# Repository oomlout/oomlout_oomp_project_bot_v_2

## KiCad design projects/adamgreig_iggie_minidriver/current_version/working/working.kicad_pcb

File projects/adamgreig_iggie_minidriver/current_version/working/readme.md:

# iggie
 
## summary 
* id: adamgreig_iggie_minidriver
* user: adamgreig
* name: iggie
* board: minidriver
* repo: https://github.com/adamgreig/iggie
* src_file_repo_kicad_pcb: minidriver/pcb/minidriver.kicad_pcb
* src_file_repo_kicad_pcb_link: https://github.com/adamgreig/iggie/tree/master/minidriver/pcb/minidriver.kicad_pcb
* src_file_repo_kicad_sch: minidriver/pcb/minidriver.kicad_sch
* src_file_repo_kicad_sch_link: https://github.com/adamgreig/iggie/tree/master/minidriver/pcb/minidriver.kicad_sch

* src_file_repo_sch: load/load.sch
* src_file_repo_sch_link: https://github.com/adamgreig/iggie/tree/master/load/load.sch
* full details link: https://github.com/oomlout/oomlout_oomp_project_bot_v_2/tree/main/projects/adamgreig_iggie_minidriver/current_version/working  

## schematic  
  
[schematic (pdf)](working_schematic.pdf) 

## pcb  

[board (pdf)](working.pdf)  

## bom_schematic
| Ref | Qnty | Value | Cmp name | Footprint | Description | Vendor | DNP | 
| --- | --- | --- | --- | --- | --- | --- | --- | 
| C1 | 1 | 4Âµ7 | C | agg:1206 |  |  |  | 
| C2, C4, C5 | 3 | 100n | C | agg:0402 |  |  |  | 
| C3 | 1 | 10Âµ | C | agg:0603 |  |  |  | 
| D1 | 1 | LED | LED | agg:0603-LED |  |  |  | 
| IC1 | 1 | TSR1-2433 | TSR1 | agg:TSR1 | TSR1 Switch Mode Regulators |  |  | 
| IC2 | 1 | STM32G070KBT6 | STM32G0xxKx | agg:LQFP-32 | STM32G0 32 pin LQFP package |  |  | 
| IC3 | 1 | 74HC4514 | 74HC4514 | agg:SOIC-24-W | 4-to-16 line decoder/demultiplexer with input latches |  |  | 
| J1 | 1 | HV_IN | CONN_01x03 | agg:MOLEX-KK-254P-03 |  |  |  | 
| J2 | 1 | HV_PSU | CONN_01x04 | agg:MOLEX-KK-254P-04 |  |  |  | 
| J3, J6, J7 | 3 | SJ2 | SJ2 | agg:SJ2 |  |  |  | 
| J4 | 1 | ANODES | CONN_01x04 | agg:MOLEX-KK-254P-04 |  |  |  | 
| J5 | 1 | CATHODES | CONN_01x04 | agg:MOLEX-KK-254P-04 |  |  |  | 
| P1 | 1 | SWD | SWD | agg:FTSH-105-01-L-DV-K | Serial Wire Debug Port |  |  | 
| Q1, Q2, Q4, Q6, Q7, Q8, Q10, Q12 | 8 | DMN60H080DS-7 | NFET | agg:SOT-23 | Generic N-channel FET |  |  | 
| Q3, Q5, Q9, Q11 | 4 | PBHV9050T,215 | PNP | agg:SOT-23 | PNP BJT Transistor |  |  | 
| R1, R2 | 2 | 100 | R | agg:0402 |  |  |  | 
| R3, R4, R9, R10 | 4 | 1M | R | agg:1206 |  |  |  | 
| R5, R6, R11, R12 | 4 | 10k | R | agg:1206 |  |  |  | 
| R7, R8, R13, R14 | 4 | 93k1 | R | agg:1206 |  |  |  | 
| R15 | 1 | 1k | R | agg:0402 |  |  |  | 
| TP1, TP2 | 2 | TESTPAD | TESTPAD | agg:KEYSTONE5016 | Test pad |  |  | 
| TP3 | 1 | TESTPAD | TESTPAD | agg:TESTPAD | Test pad |  |  | 
| TP4 | 1 | TESTPAD | TESTPAD | agg:SIL-254P-01 | Test pad |  |  | 
| X1, X2, X3, X4 | 4 | M3 MOUNT | PART | agg:M3_MOUNT | Generic placeholder part |  |  |

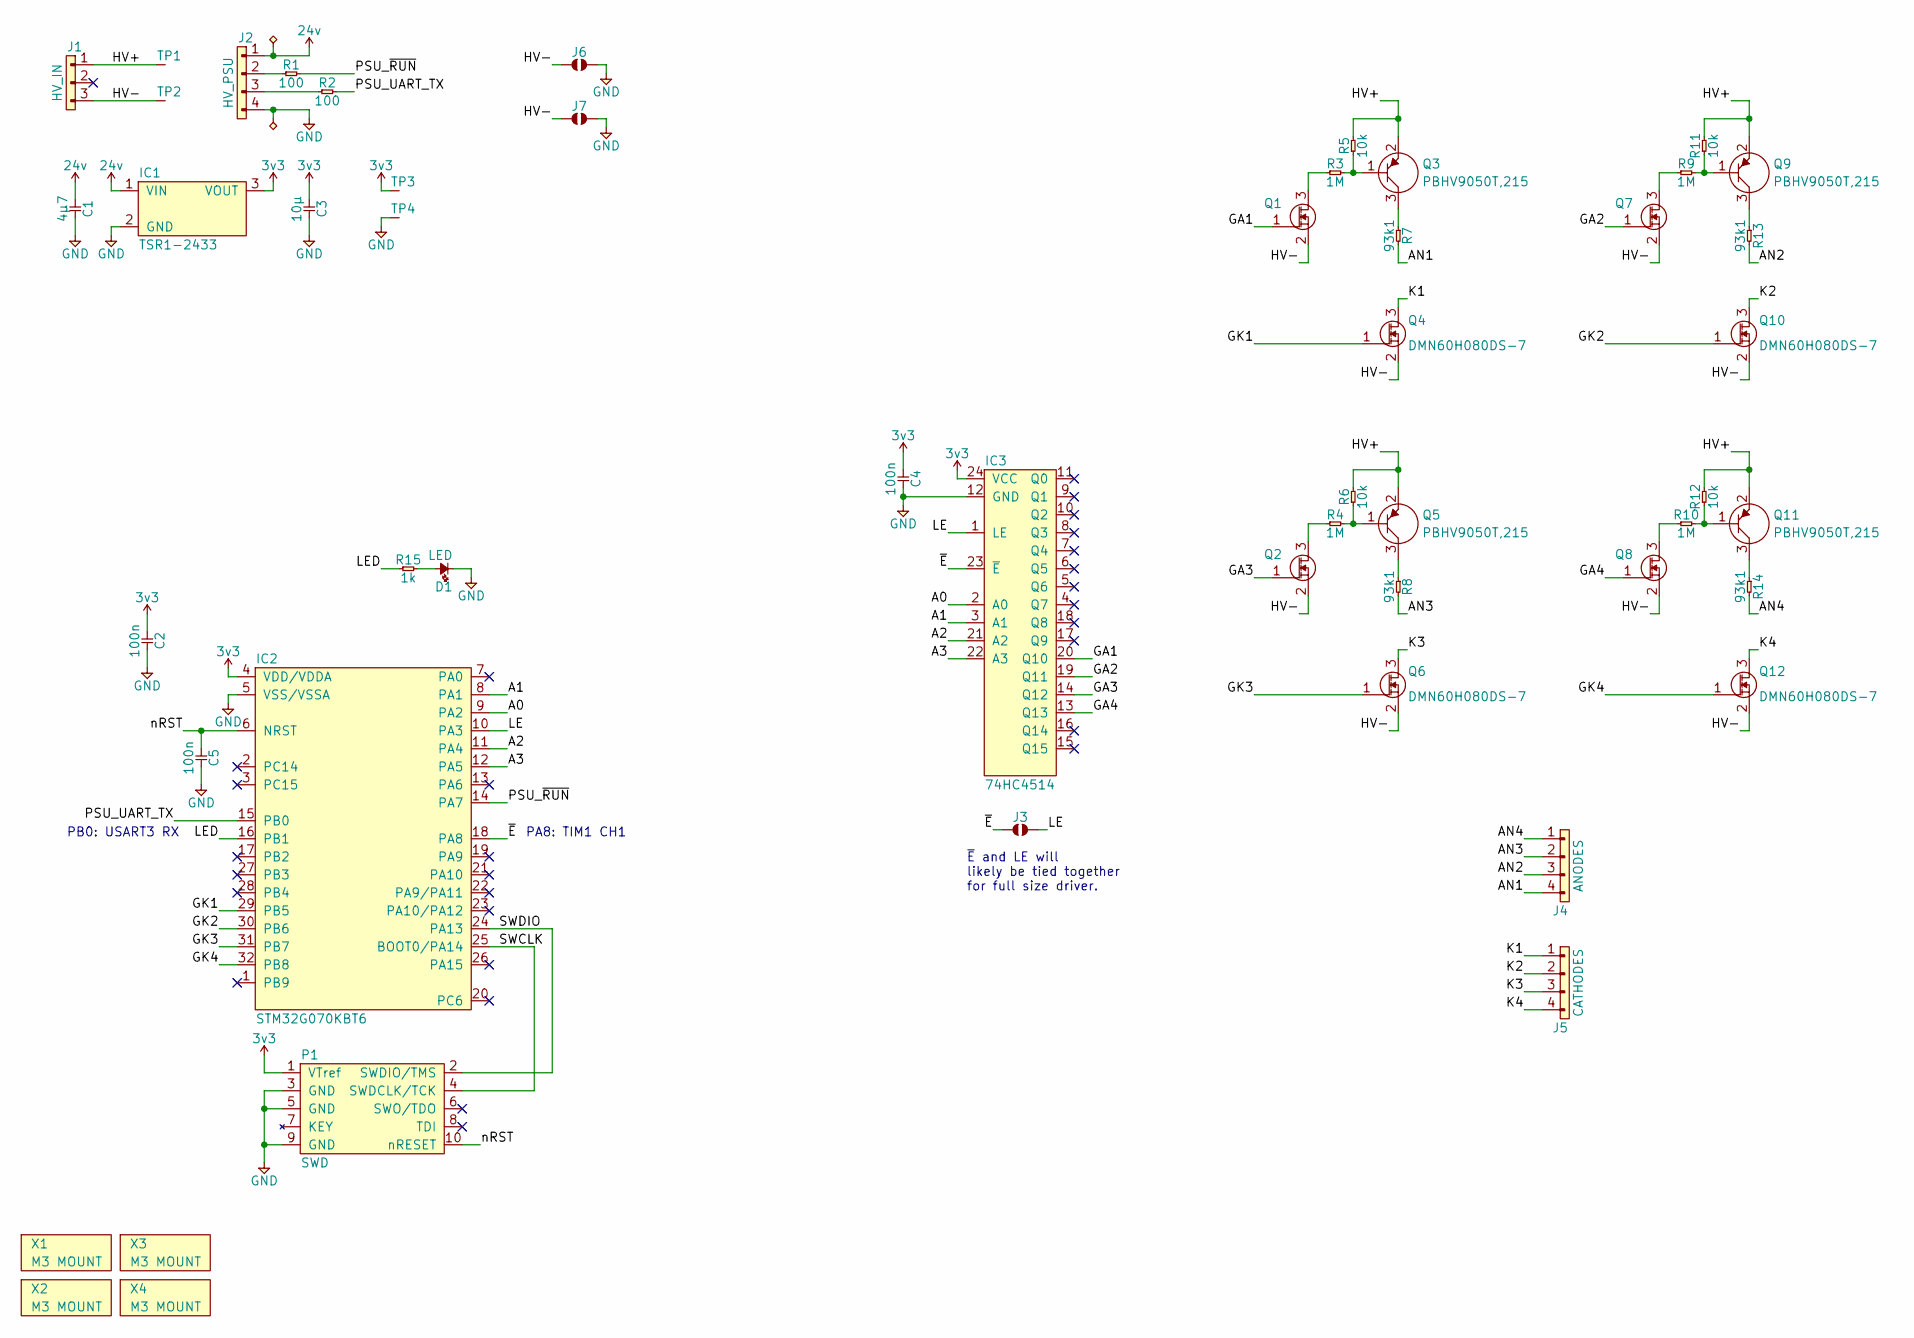
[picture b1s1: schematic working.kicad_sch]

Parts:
C1: 4µ7; 1206; Voltage 50V; Farnell 2112859
C2, C4, C5: 100n; 0402; Voltage 16V; Farnell 2810260
C3: 10µ; 0603; Voltage 6.3V; Farnell 3013391
D1: LED; 0603-LED; Farnell 2290328
IC1: TSR1-2433; TSR1; Farnell 1696319
IC2: STM32G070KBT6; LQFP-32; Farnell 3365394
IC3: 74HC4514; SOIC-24-W; Farnell 2444987
J1: HV_IN; MOLEX-KK-254P-03; Farnell 1360131
J2: HV_PSU; MOLEX-KK-254P-04; Farnell 1360132
J3, J6, J7: SJ2
J4: ANODES; MOLEX-KK-254P-04; Farnell 1360132
J5: CATHODES; MOLEX-KK-254P-04; Farnell 1360132
P1: SWD; FTSH-105-01-L-DV-K; Farnell 2856437
Q1, Q2, Q4, Q6, Q7, Q8, Q10, Q12: DMN60H080DS-7; SOT-23; Farnell 3127344
Q3, Q5, Q9, Q11: PBHV9050T,215; SOT-23; Farnell 1829318
R1, R2: 100; 0402; Voltage 50V; Farnell 9239111
R3, R4, R9, R10: 1M; 1206; Voltage 500V; Farnell 1750877
R5, R6, R11, R12: 10k; 1206; Voltage 500V; Farnell 1750850
R7, R8, R13, R14: 93k1; 1206; Voltage 500V; Farnell 2327389
R15: 1k; 0402; Voltage 50V; Farnell 2331474
TP1, TP2: TESTPAD; KEYSTONE5016; Farnell 2292858
TP3: TESTPAD
TP4: TESTPAD; SIL-254P-01
X1, X2, X3, X4: M3 MOUNT; M3_MOUNT

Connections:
3v3: C2.1, C3.1, C4.1, IC1.3 (VOUT), IC2.4 (VDD/VDDA), IC3.24 (VCC), P1.1 (VTref), TP3.1 (TP)
24v: C1.1, IC1.1 (VIN), J2.1
/A0: IC2.9 (PA2), IC3.2 (A0)
/A1: IC2.8 (PA1), IC3.3 (A1)
/A2: IC2.11 (PA4), IC3.21 (A2)
/A3: IC2.12 (PA5), IC3.22 (A3)
/AN1: J4.4, R7.2
/AN2: J4.3, R13.2
/AN3: J4.2, R8.2
/AN4: J4.1, R14.2
/GA1: IC3.20 (Q10), Q1.1 (G)
/GA2: IC3.19 (Q11), Q7.1 (G)
/GA3: IC3.14 (Q12), Q2.1 (G)
/GA4: IC3.13 (Q13), Q8.1 (G)
/GK1: IC2.29 (PB5), Q4.1 (G)
/GK2: IC2.30 (PB6), Q10.1 (G)
/GK3: IC2.31 (PB7), Q6.1 (G)
/GK4: IC2.32 (PB8), Q12.1 (G)
/HV+: J1.1, Q3.2 (E), Q5.2 (E), Q9.2 (E), Q11.2 (E), R5.2, R6.2, R11.2, R12.2, TP1.1 (TP)
/HV-: J1.3, J6.1, J7.1, Q1.2 (S), Q2.2 (S), Q4.2 (S), Q6.2 (S), Q7.2 (S), Q8.2 (S), Q10.2 (S), Q12.2 (S), TP2.1 (TP)
/K1: J5.1, Q4.3 (D)
/K2: J5.2, Q10.3 (D)
/K3: J5.3, Q6.3 (D)
/K4: J5.4, Q12.3 (D)
/LE: IC2.10 (PA3), IC3.1 (LE), J3.2
/LED: IC2.16 (PB1), R15.1
/PSU_UART_TX: IC2.15 (PB0), R2.2
/PSU_~RUN: IC2.14 (PA7), R1.2
/SWCLK: IC2.25 (BOOT0/PA14), P1.4 (SWDCLK/TCK)
/SWDIO: IC2.24 (PA13), P1.2 (SWDIO/TMS)
/nRST: C5.1, IC2.6 (NRST), P1.10 (nRESET)
/~E: IC2.18 (PA8), IC3.23 (~E), J3.1
GND: C1.2, C2.2, C3.2, C4.2, C5.2, D1.1, IC1.2 (GND), IC2.5 (VSS/VSSA), IC3.12 (GND), J2.4, J6.2, J7.2, P1.3 (GND), P1.5 (GND), P1.9 (GND), TP4.1 (TP)
unnamed: D1.2, R15.2
unnamed: J2.2, R1.1
unnamed: J2.3, R2.1
unnamed: Q1.3 (D), R3.1
unnamed: Q2.3 (D), R4.1
unnamed: Q3.1 (B), R3.2, R5.1
unnamed: Q3.3 (C), R7.1
unnamed: Q5.1 (B), R4.2, R6.1
unnamed: Q5.3 (C), R8.1
unnamed: Q7.3 (D), R9.1
unnamed: Q8.3 (D), R10.1
unnamed: Q9.1 (B), R9.2, R11.1
unnamed: Q9.3 (C), R13.1
unnamed: Q11.1 (B), R10.2, R12.1
unnamed: Q11.3 (C), R14.1
no_connect_49: IC2.1 (PB9)
no_connect_50: IC2.13 (PA6)
no_connect_51: IC2.17 (PB2)
no_connect_52: IC2.19 (PA9)
no_connect_53: IC2.2 (PC14)
no_connect_54: IC2.20 (PC6)
no_connect_55: IC2.21 (PA10)
no_connect_56: IC2.22 (PA9/PA11)
no_connect_57: IC2.23 (PA10/PA12)
no_connect_58: IC2.26 (PA15)
no_connect_59: IC2.27 (PB3)
no_connect_60: IC2.28 (PB4)
no_connect_61: IC2.3 (PC15)
no_connect_62: IC2.7 (PA0)
no_connect_63: IC3.10 (Q2)
no_connect_64: IC3.11 (Q0)
no_connect_65: IC3.15 (Q15)
no_connect_66: IC3.16 (Q14)
no_connect_67: IC3.17 (Q9)
no_connect_68: IC3.18 (Q8)
no_connect_69: IC3.4 (Q7)
no_connect_70: IC3.5 (Q6)
no_connect_71: IC3.6 (Q5)
no_connect_72: IC3.7 (Q4)
no_connect_73: IC3.8 (Q3)
no_connect_74: IC3.9 (Q1)
no_connect_76: P1.6 (SWO/TDO)
no_connect_77: P1.8 (TDI)

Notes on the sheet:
PA8: TIM1 CH1
PB0: USART3 RX
~{E} and LE will likely be tied together for full size driver.

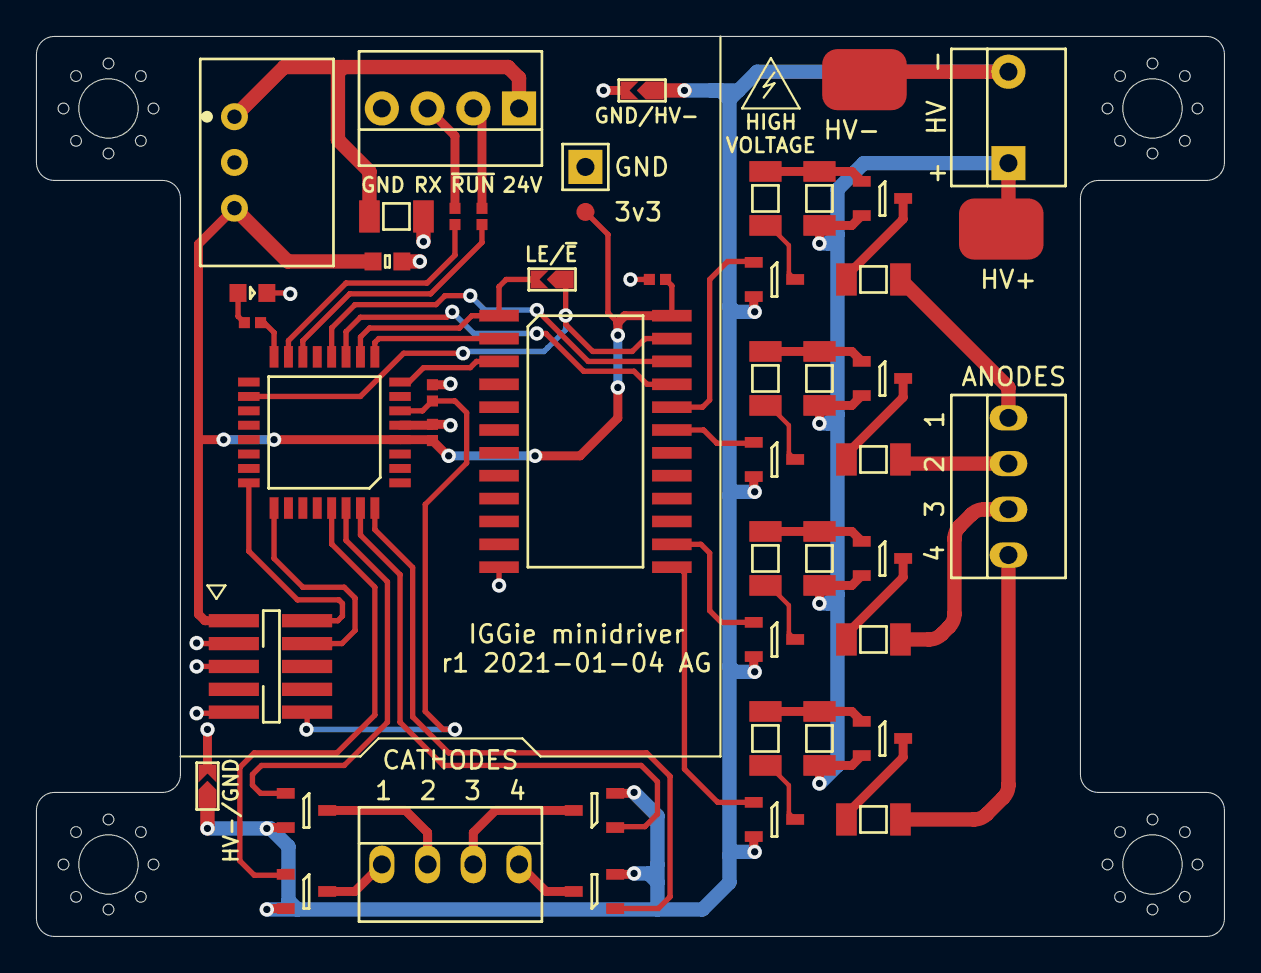
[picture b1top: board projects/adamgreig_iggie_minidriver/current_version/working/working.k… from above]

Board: 2 copper layers, 66.0 x 50.0 mm, 52 parts (0 on the bottom side), 48 nets.

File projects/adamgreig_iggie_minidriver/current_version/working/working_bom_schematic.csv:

"Source:","C:\gh\oomlout_oomp_project_bot_v_2\projects\adamgreig_iggie_minidriver\current_version\working\working.kicad_sch"
"Date:","17/09/2023 22:09:59"
"Tool:","Eeschema 7.0.6"
"Generator:","C:/Program Files/KiCad/7.0/bin/scripting/plugins/bom_csv_grouped_by_value_with_fp.py"
"Component Count:","52"
"Ref","Qnty","Value","Cmp name","Footprint","Description","Vendor","DNP"
"C1","1","4µ7","C","agg:1206","","",""
"C2, C4, C5","3","100n","C","agg:0402","","",""
"C3","1","10µ","C","agg:0603","","",""
"D1","1","LED","LED","agg:0603-LED","","",""
"IC1","1","TSR1-2433","TSR1","agg:TSR1","TSR1 Switch Mode Regulators","",""
"IC2","1","STM32G070KBT6","STM32G0xxKx","agg:LQFP-32","STM32G0 32 pin LQFP package","",""
"IC3","1","74HC4514","74HC4514","agg:SOIC-24-W","4-to-16 line decoder/demultiplexer with input latches","",""
"J1","1","HV_IN","CONN_01x03","agg:MOLEX-KK-254P-03","","",""
"J2","1","HV_PSU","CONN_01x04","agg:MOLEX-KK-254P-04","","",""
"J3, J6, J7","3","SJ2","SJ2","agg:SJ2","","",""
"J4","1","ANODES","CONN_01x04","agg:MOLEX-KK-254P-04","","",""
"J5","1","CATHODES","CONN_01x04","agg:MOLEX-KK-254P-04","","",""
"P1","1","SWD","SWD","agg:FTSH-105-01-L-DV-K","Serial Wire Debug Port","",""
"Q1, Q2, Q4, Q6, Q7, Q8, Q10, Q12","8","DMN60H080DS-7","NFET","agg:SOT-23","Generic N-channel FET","",""
"Q3, Q5, Q9, Q11","4","PBHV9050T,215","PNP","agg:SOT-23","PNP BJT Transistor","",""
"R1, R2","2","100","R","agg:0402","","",""
"R3, R4, R9, R10","4","1M","R","agg:1206","","",""
"R5, R6, R11, R12","4","10k","R","agg:1206","","",""
"R7, R8, R13, R14","4","93k1","R","agg:1206","","",""
"R15","1","1k","R","agg:0402","","",""
"TP1, TP2","2","TESTPAD","TESTPAD","agg:KEYSTONE5016","Test pad","",""
"TP3","1","TESTPAD","TESTPAD","agg:TESTPAD","Test pad","",""
"TP4","1","TESTPAD","TESTPAD","agg:SIL-254P-01","Test pad","",""
"X1, X2, X3, X4","4","M3 MOUNT","PART","agg:M3_MOUNT","Generic placeholder part","",""

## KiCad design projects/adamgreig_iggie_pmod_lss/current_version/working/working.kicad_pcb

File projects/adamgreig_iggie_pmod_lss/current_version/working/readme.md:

# iggie
 
## summary 
* id: adamgreig_iggie_pmod_lss
* user: adamgreig
* name: iggie
* board: pmod_lss
* repo: https://github.com/adamgreig/iggie
* src_file_repo_kicad_pcb: pmod_lss/pmod_lss.kicad_pcb
* src_file_repo_kicad_pcb_link: https://github.com/adamgreig/iggie/tree/master/pmod_lss/pmod_lss.kicad_pcb
* src_file_repo_kicad_sch: pmod_lss/pmod_lss.kicad_sch
* src_file_repo_kicad_sch_link: https://github.com/adamgreig/iggie/tree/master/pmod_lss/pmod_lss.kicad_sch

* src_file_repo_sch: load/load.sch
* src_file_repo_sch_link: https://github.com/adamgreig/iggie/tree/master/load/load.sch
* full details link: https://github.com/oomlout/oomlout_oomp_project_bot_v_2/tree/main/projects/adamgreig_iggie_pmod_lss/current_version/working  

## schematic  
  
[schematic (pdf)](working_schematic.pdf) 

## pcb  

[board (pdf)](working.pdf)  

## working_bom
| Id | Designator | Footprint | Quantity | Designation | Supplier and ref |  | None | 
| --- | --- | --- | --- | --- | --- | --- | --- | 
| 1 | J3 | DIL-254P-12 | 1 | PMOD |  |  | [''] | 
| 2 | J2,J1 | MOLEX-KK-254P-03 | 2 | HV |  |  | [''] | 
| 3 | Q9,Q15,Q4,Q10,Q1,Q2,Q13,Q16,Q3,Q7,Q5,Q6,Q12,Q11,Q8,Q14 | SOT-23 | 16 | DMN60H080DS-7 |  |  | [''] | 
| 4 | J4 | DIL-254P-16 | 1 | CATHODES |  |  | [''] | 
| 5 | C2,C1 | 0603 | 2 | 100n |  |  | [''] | 
| 6 | IC1 | SOIC-24-W | 1 | 74HC4514 |  |  | [''] | 
| 7 | J5 | SJ2 | 1 | SJ2 |  |  | [''] | 

## bom_schematic
| Ref | Qnty | Value | Cmp name | Footprint | Description | Vendor | DNP | 
| --- | --- | --- | --- | --- | --- | --- | --- | 
| C1, C2 | 2 | 100n | C | agg:0603 |  |  |  | 
| IC1 | 1 | 74HC4514 | 74HC4514 | agg:SOIC-24-W | 4-to-16 line decoder/demultiplexer with input latches |  |  | 
| J1, J2 | 2 | HV | CONN_01x03 | agg:MOLEX-KK-254P-03 |  |  |  | 
| J3 | 1 | PMOD | CONN_02x06 | agg:DIL-254P-12 |  |  |  | 
| J4 | 1 | CATHODES | CONN_02x08 | agg:DIL-254P-16 |  |  |  | 
| J5 | 1 | SJ2 | SJ2 | agg:SJ2 |  |  |  | 
| Q1, Q2, Q3, Q4, Q5, Q6, Q7, Q8, Q9, Q10, Q11, Q12, Q13, Q14, Q15, Q16 | 16 | DMN60H080DS-7 | NFET | agg:SOT-23 | Generic N-channel FET |  |  |

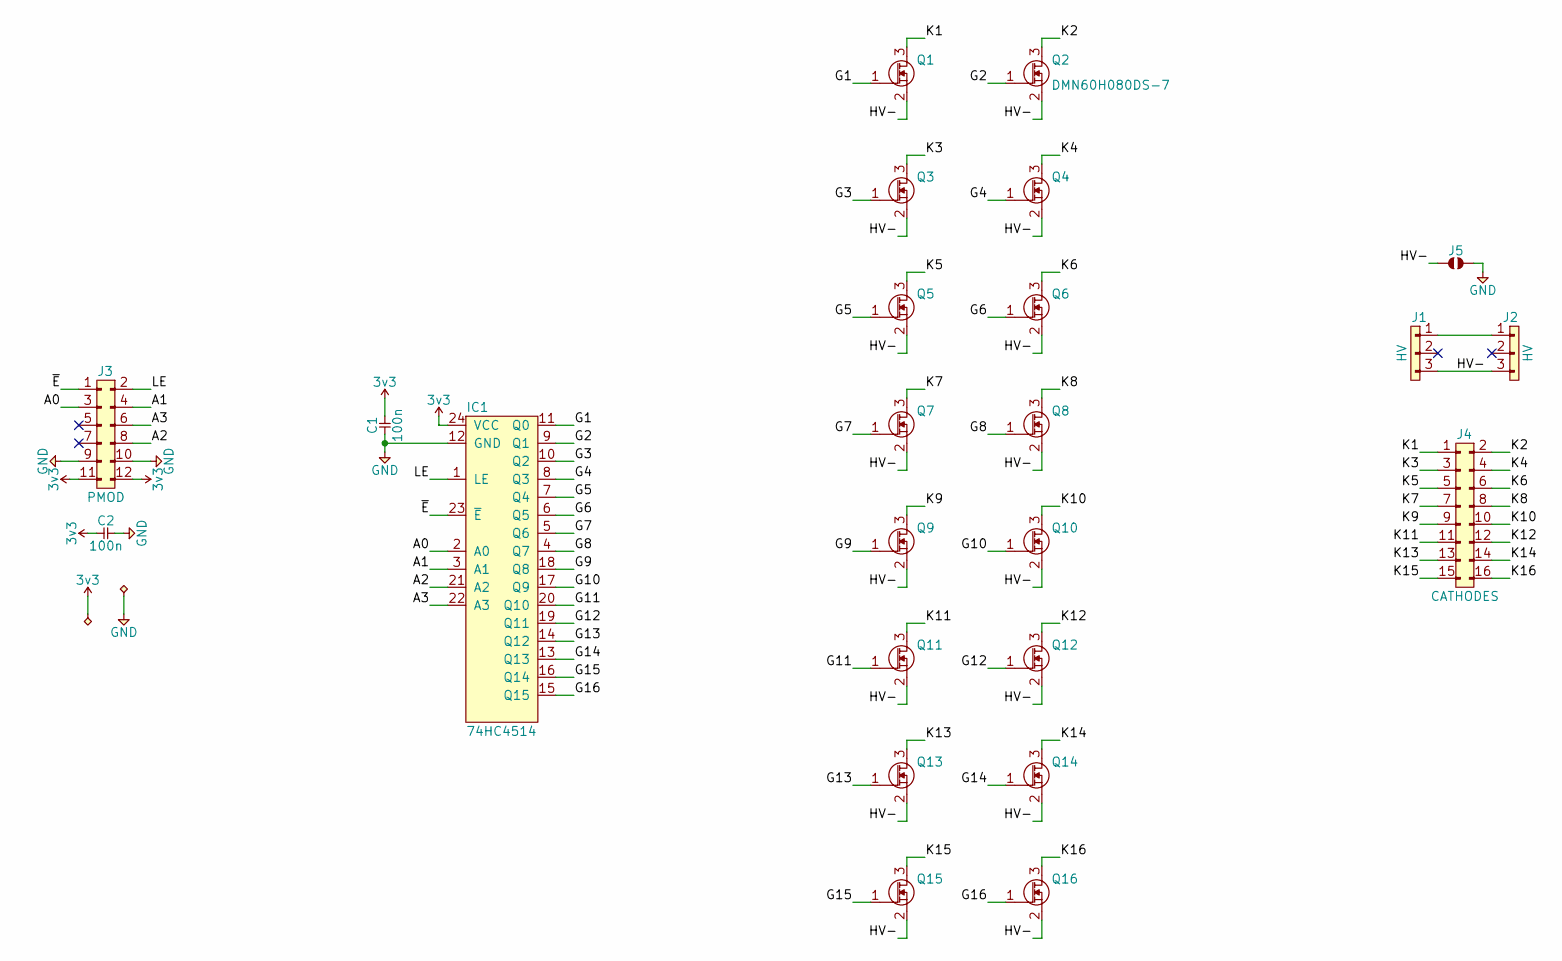
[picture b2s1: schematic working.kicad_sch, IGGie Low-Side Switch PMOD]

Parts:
C1, C2: 100n; 0603
IC1: 74HC4514; SOIC-24-W; Farnell 2444987
J1, J2: HV; MOLEX-KK-254P-03; Farnell 1360131
J3: PMOD; DIL-254P-12; Farnell 2779668
J4: CATHODES; DIL-254P-16; Farnell 2578721
J5: SJ2
Q1, Q2, Q3, Q4, Q5, Q6, Q7, Q8, Q9, Q10, Q11, Q12, Q13, Q14, Q15, Q16: DMN60H080DS-7; SOT-23; Farnell 3127344

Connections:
3v3: C1.2, C2.1, IC1.24 (VCC), J3.11, J3.12
/A0: IC1.2 (A0), J3.3
/A1: IC1.3 (A1), J3.4
/A2: IC1.21 (A2), J3.8
/A3: IC1.22 (A3), J3.6
/G1: IC1.11 (Q0), Q1.1 (G)
/G2: IC1.9 (Q1), Q2.1 (G)
/G3: IC1.10 (Q2), Q3.1 (G)
/G4: IC1.8 (Q3), Q4.1 (G)
/G5: IC1.7 (Q4), Q5.1 (G)
/G6: IC1.6 (Q5), Q6.1 (G)
/G7: IC1.5 (Q6), Q7.1 (G)
/G8: IC1.4 (Q7), Q8.1 (G)
/G9: IC1.18 (Q8), Q9.1 (G)
/G10: IC1.17 (Q9), Q10.1 (G)
/G11: IC1.20 (Q10), Q11.1 (G)
/G12: IC1.19 (Q11), Q12.1 (G)
/G13: IC1.14 (Q12), Q13.1 (G)
/G14: IC1.13 (Q13), Q14.1 (G)
/G15: IC1.16 (Q14), Q15.1 (G)
/G16: IC1.15 (Q15), Q16.1 (G)
/HV-: J1.3, J2.3, J5.1, Q1.2 (S), Q2.2 (S), Q3.2 (S), Q4.2 (S), Q5.2 (S), Q6.2 (S), Q7.2 (S), Q8.2 (S), Q9.2 (S), Q10.2 (S), Q11.2 (S), Q12.2 (S), Q13.2 (S), Q14.2 (S), Q15.2 (S), Q16.2 (S)
/K1: J4.1, Q1.3 (D)
/K2: J4.2, Q2.3 (D)
/K3: J4.3, Q3.3 (D)
/K4: J4.4, Q4.3 (D)
/K5: J4.5, Q5.3 (D)
/K6: J4.6, Q6.3 (D)
/K7: J4.7, Q7.3 (D)
/K8: J4.8, Q8.3 (D)
/K9: J4.9, Q9.3 (D)
/K10: J4.10, Q10.3 (D)
/K11: J4.11, Q11.3 (D)
/K12: J4.12, Q12.3 (D)
/K13: J4.13, Q13.3 (D)
/K14: J4.14, Q14.3 (D)
/K15: J4.15, Q15.3 (D)
/K16: J4.16, Q16.3 (D)
/LE: IC1.1 (LE), J3.2
/~E: IC1.23 (~E), J3.1
GND: C1.1, C2.2, IC1.12 (GND), J3.9, J3.10, J5.2
unnamed: J1.1, J2.1

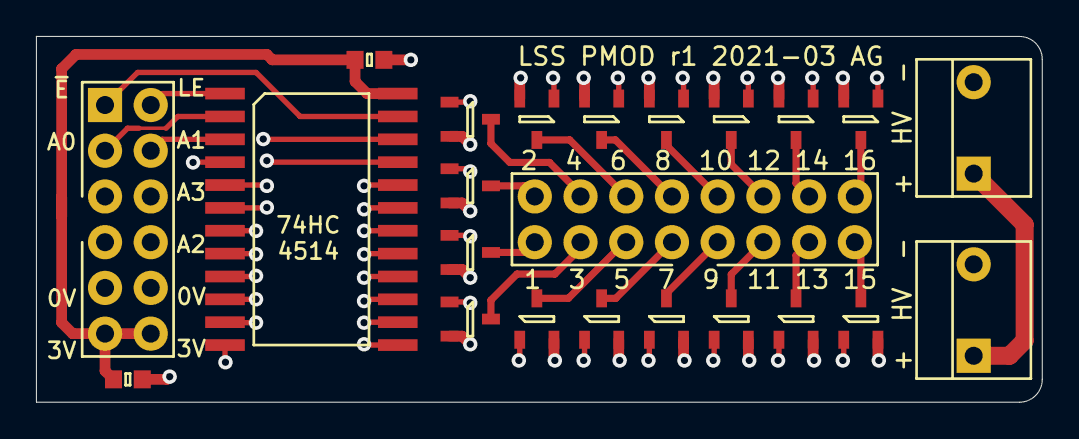
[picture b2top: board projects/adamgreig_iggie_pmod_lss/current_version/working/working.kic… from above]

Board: 4 copper layers, 55.9 x 20.3 mm, 24 parts (1 on the bottom side), 42 nets.

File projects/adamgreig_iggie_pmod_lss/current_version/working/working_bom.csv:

"Id";"Designator";"Footprint";"Quantity";"Designation";"Supplier and ref";
1;"J3";"DIL-254P-12";1;"PMOD";;;
2;"J2,J1";"MOLEX-KK-254P-03";2;"HV";;;
3;"Q9,Q15,Q4,Q10,Q1,Q2,Q13,Q16,Q3,Q7,Q5,Q6,Q12,Q11,Q8,Q14";"SOT-23";16;"DMN60H080DS-7";;;
4;"J4";"DIL-254P-16";1;"CATHODES";;;
5;"C2,C1";"0603";2;"100n";;;
6;"IC1";"SOIC-24-W";1;"74HC4514";;;
7;"J5";"SJ2";1;"SJ2";;;

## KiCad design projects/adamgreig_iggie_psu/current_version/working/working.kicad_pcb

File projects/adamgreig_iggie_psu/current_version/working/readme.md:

# iggie
 
## summary 
* id: adamgreig_iggie_psu
* user: adamgreig
* name: iggie
* board: psu
* repo: https://github.com/adamgreig/iggie
* src_file_repo_kicad_pcb: psu/pcb/psu.kicad_pcb
* src_file_repo_kicad_pcb_link: https://github.com/adamgreig/iggie/tree/master/psu/pcb/psu.kicad_pcb
* src_file_repo_kicad_sch: pmod_lss/pmod_lss.kicad_sch
* src_file_repo_kicad_sch_link: https://github.com/adamgreig/iggie/tree/master/pmod_lss/pmod_lss.kicad_sch

* src_file_repo_sch: load/load.sch
* src_file_repo_sch_link: https://github.com/adamgreig/iggie/tree/master/load/load.sch
* full details link: https://github.com/oomlout/oomlout_oomp_project_bot_v_2/tree/main/projects/adamgreig_iggie_psu/current_version/working  

## schematic  
  
[schematic (pdf)](working_schematic.pdf) 

## pcb  

[board (pdf)](working.pdf)  

## working_bom
| Id | Designator | Footprint | Quantity | Designation | Supplier and ref |  | None | 
| --- | --- | --- | --- | --- | --- | --- | --- | 
| 1 | C101,C222 | 0603 | 2 | 100p |  |  | [''] | 
| 2 | C102,C106,C109,C110,C209,C208 | 1210 | 6 | 10Âµ |  |  | [''] | 
| 3 | C103,C104,C105,C108,C202,C215,C224,C225,C203,C213,C228,C113,C112 | 0603 | 13 | 100n |  |  | [''] | 
| 4 | C107,C111,C204,C218,C223,C226,C229 | 0603 | 7 | 1Âµ |  |  | [''] | 
| 5 | C205,C227 | 0805 | 2 | 10n |  |  | [''] | 
| 6 | D101 | DO-214AC-SMA | 1 | SMAJ58A |  |  | [''] | 
| 7 | D104,D105,D108,D103,D107 | 0603-LED | 5 | GRN |  |  | [''] | 
| 8 | D109,D110,D111 | 0603 | 3 | ESD_DIODE |  |  | [''] | 
| 9 | D201,D202 | SOD-123 | 2 | NTS245SFT1G |  |  | [''] | 
| 10 | IC101 | TSR1 | 1 | TSR 1-24150 |  |  | [''] | 
| 11 | IC103 | TSR1 | 1 | TSR 1-2450 |  |  | [''] | 
| 12 | IC104 | SOT-23-5 | 1 | NCP161 |  |  | [''] | 
| 13 | IC202,IC206,IC207 | SOT-23-5 | 3 | AD8605 |  |  | [''] | 
| 14 | J102 | MOLEX-KK-254P-04 | 1 | CTRL |  |  | [''] | 
| 15 | P101 | FTSH-105-01-L-DV-K | 1 | SWD |  |  | [''] | 
| 16 | R101,R103,R104,R109,R206,R207,R217 | 0603 | 7 | 10k |  |  | [''] | 
| 17 | R102,R211,R226,R202,R203,R212,R227 | 0603 | 7 | 100k |  |  | [''] | 
| 18 | R105,R106,R107,R108,R110,R111,R208,R209,R210 | 0603 | 9 | 1k |  |  | [''] | 
| 19 | TP101,TP103,TP104,TP105,TP204,TP205,TP201 | TESTPAD | 7 | TESTPAD |  |  | [''] | 
| 20 | X101,X102,X103,X104 | M3_MOUNT | 4 | M3 MOUNT |  |  | [''] | 
| 21 | Q202 | SOT-23 | 1 | PBHV9050T |  |  | [''] | 
| 22 | IC204 | SOT-23-5 | 1 | AD8065 |  |  | [''] | 
| 23 | C201,C211,C210,C212 | 1206 | 4 | 1Âµ |  |  | [''] | 
| 24 | IC201,IC205 | SOT-23-5 | 2 | INA139 |  |  | [''] | 
| 25 | TP206,TP203,TP102,TP202,TP207 | KEYSTONE5016 | 5 | TESTPAD |  |  | [''] | 
| 26 | J101 | BARRELJACK | 1 | PWR_IN |  |  | [''] | 
| 27 | Y101 | XTAL-25x20 | 1 | 25M |  |  | [''] | 
| 28 | J103 | MOLEX-KK-254P-03 | 1 | HV_OUT |  |  | [''] | 
| 29 | R221,R220,R218,R219 | 1206 | 4 | 100k |  |  | [''] | 
| 30 | R222,R224,R225,R215,R214,R223,R216,R213 | 1206 | 8 | 499k |  |  | [''] | 
| 31 | C207,C206 | PANASONIC-SMDCAP-G | 2 | 100Âµ |  |  | [''] | 
| 32 | C219,C220,C221 | 2220 | 3 | 1Âµ |  |  | [''] | 
| 33 | R228 | 1206 | 1 | 500m |  |  | [''] | 
| 34 | D204,D205 | SOT-23 | 2 | ADR5045 |  |  | [''] | 
| 35 | C214 | 1206 | 1 | 10n |  |  | [''] | 
| 36 | R204 | 1206 | 1 | 4R7 |  |  | [''] | 
| 37 | C217,C216 | PANASONIC-SMDCAP-K | 2 | 68Âµ |  |  | [''] | 
| 38 | IC203 | SOT-23-5 | 1 | MCP1416 |  |  | [''] | 
| 39 | T201 | GA3459-BL | 1 | GA3459-BL |  |  | [''] | 
| 40 | D203 | DPAK_DIODE | 1 | STTH512B |  |  | [''] | 
| 41 | R201,R205 | 1206 | 2 | 10m |  |  | [''] | 
| 42 | Q201 | D2PAK_GDS | 1 | STB45N60DM2AG |  |  | [''] | 
| 43 | X106,X107 | hv | 2 | HV SIGN |  |  | [''] | 
| 44 | D102 | DO-214AB-SMC | 1 | VSSC520S-M3/9AT |  |  | [''] | 
| 45 | J104 | MOLEX-PICOBLADE-53398-0471 | 1 | UART |  |  | [''] | 
| 46 | IC105 | SOIC-8 | 1 | ADuM1201 |  |  | [''] | 
| 47 | IC102 | LQFP-32 | 1 | STM32F334K8T6 |  |  | [''] | 
| 48 | D106 | 0603-LED | 1 | RED |  |  | [''] | 
| 49 | L101 | 0603 | 1 | FB |  |  | [''] | 

## bom_schematic
| Ref | Qnty | Value | Cmp name | Footprint | Description | Vendor | DNP | 
| --- | --- | --- | --- | --- | --- | --- | --- | 
| C101 | 1 | 100p | C-agg | agg:0603 |  |  |  | 
| C102, C106, C109, C110 | 4 | 10Âµ | C-agg | agg:1210 |  |  |  | 
| C103, C104, C105, C108, C112, C113 | 6 | 100n | C-agg | agg:0603 |  |  |  | 
| C107, C111 | 2 | 1Âµ | C-agg | agg:0603 |  |  |  | 
| D101 | 1 | SMAJ58A | SCHOTTKY-agg | agg:DO-214AC-SMA |  |  |  | 
| D102 | 1 | VSSC520S-M3/9AT | SCHOTTKY-agg | agg:DO-214AB-SMC |  |  |  | 
| D103, D104, D105, D107, D108 | 5 | GRN | LED-agg | agg:0603-LED |  |  |  | 
| D106 | 1 | RED | LED-agg | agg:0603-LED |  |  |  | 
| D109, D110, D111 | 3 | ESD_DIODE | ESD_DIODE-agg | agg:0603 |  |  |  | 
| IC101 | 1 | TSR 1-24150 | TSR1-agg | agg:TSR1 |  |  |  | 
| IC102 | 1 | STM32F334K8T6 | STM32F3xxKxTx-agg | agg:LQFP-32 |  |  |  | 
| IC103 | 1 | TSR 1-2450 | TSR1-agg | agg:TSR1 |  |  |  | 
| IC104 | 1 | NCP161 | NCP161-agg | agg:SOT-23-5 |  |  |  | 
| IC105 | 1 | ADuM1201 | ADuM1201-agg | agg:SOIC-8 |  |  |  | 
| J101 | 1 | PWR_IN | BarrelJack-agg | agg:BARRELJACK |  |  |  | 
| J102 | 1 | CTRL | CONN_01x04-agg | agg:MOLEX-KK-254P-04 |  |  |  | 
| J103 | 1 | HV_OUT | CONN_01x03-agg | agg:MOLEX-KK-254P-03 |  |  |  | 
| J104 | 1 | UART | CONN_01x04-agg | agg:MOLEX-PICOBLADE-53398-0471 |  |  |  | 
| L101 | 1 | FB | L-agg | agg:0603 |  |  |  | 
| P101 | 1 | SWD | SWD-agg | agg:FTSH-105-01-L-DV-K |  |  |  | 
| R101, R103, R104, R109 | 4 | 10k | R-agg | agg:0603 |  |  |  | 
| R102 | 1 | 100k | R-agg | agg:0603 |  |  |  | 
| R105, R106, R107, R108, R110, R111 | 6 | 1k | R-agg | agg:0603 |  |  |  | 
| TP101, TP103, TP104, TP105 | 4 | TESTPAD | TESTPAD-agg | agg:TESTPAD |  |  |  | 
| TP102 | 1 | TESTPAD | TESTPAD-agg | agg:KEYSTONE5016 |  |  |  | 
| X101, X102, X103, X104 | 4 | M3 MOUNT | PART-agg | agg:M3_MOUNT |  |  |  | 
| X105 | 1 | MAINS PSU | PART-agg |  |  |  |  | 
| X106, X107 | 2 | HV SIGN | PART-agg | psu:hv |  |  |  | 
| Y101 | 1 | 25M | TCXO_ST-agg | agg:XTAL-25x20 |  |  |  |

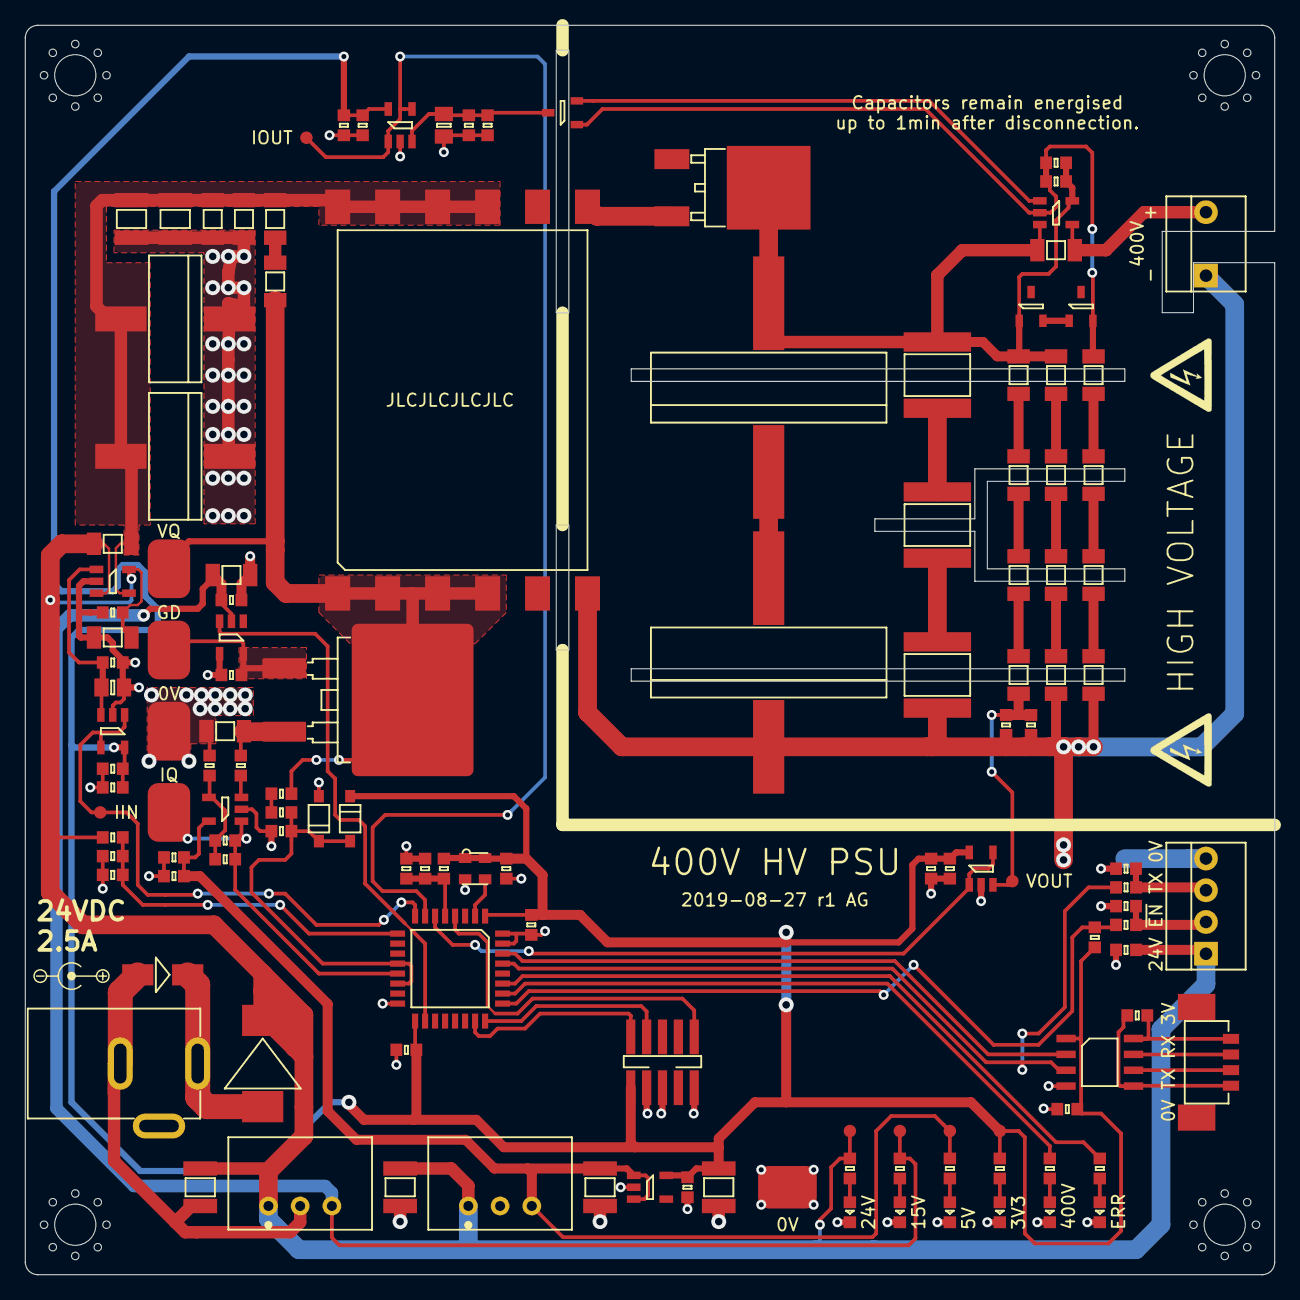
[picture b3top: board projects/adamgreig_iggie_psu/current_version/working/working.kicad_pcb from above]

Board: 2 copper layers, 100.0 x 100.0 mm, 137 parts (0 on the bottom side), 64 nets.

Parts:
C101, C222: 100p; 0603
C102, C106, C109, C110, C208, C209: 10µ; 1210
C103, C104, C105, C108, C112, C113, C202, C203, C213, C215, C224, C225, C228: 100n; 0603
C107, C111, C204, C218, C223, C226, C229: 1µ; 0603
C201, C210, C211, C212: 1µ; 1206
C205, C227: 10n; 0805
C206, C207: 100µ; PANASONIC-SMDCAP-G
C214: 10n; 1206
C216, C217: 68µ; PANASONIC-SMDCAP-K
C219, C220, C221: 1µ; 2220
D101: SMAJ58A; DO-214AC-SMA
D102: VSSC520S-M3/9AT; DO-214AB-SMC
D103, D104, D105, D107, D108: GRN; 0603-LED
D106: RED; 0603-LED
D109, D110, D111: ESD_DIODE; 0603
D201, D202: NTS245SFT1G; SOD-123
D203: STTH512B; DPAK_DIODE
D204, D205: ADR5045; SOT-23
IC101: TSR 1-24150; TSR1
IC102: STM32F334K8T6; LQFP-32
IC103: TSR 1-2450; TSR1
IC104: NCP161; SOT-23-5
IC105: ADuM1201; SOIC-8
IC201, IC205: INA139; SOT-23-5
IC202, IC206, IC207: AD8605; SOT-23-5
IC203: MCP1416; SOT-23-5
IC204: AD8065; SOT-23-5
J101: PWR_IN; BARRELJACK
J102: CTRL; MOLEX-KK-254P-04
J103: HV_OUT; MOLEX-KK-254P-03
J104: UART; MOLEX-PICOBLADE-53398-0471
L101: FB; 0603
P101: SWD; FTSH-105-01-L-DV-K
Q201: STB45N60DM2AG; D2PAK_GDS
Q202: PBHV9050T; SOT-23
R101, R103, R104, R109, R206, R207, R217: 10k; 0603
R102, R202, R203, R211, R212, R226, R227: 100k; 0603
R105, R106, R107, R108, R110, R111, R208, R209, R210: 1k; 0603
R201, R205: 10m; 1206
R204: 4R7; 1206
R213, R214, R215, R216, R222, R223, R224, R225: 499k; 1206
R218, R219, R220, R221: 100k; 1206
R228: 500m; 1206
T201: GA3459-BL
TP101, TP103, TP104, TP105, TP201, TP204, TP205: TESTPAD
TP102, TP202, TP203, TP206, TP207: TESTPAD; KEYSTONE5016
X101, X102, X103, X104: M3 MOUNT; M3_MOUNT
X106, X107: HV SIGN; hv
Y101: 25M; XTAL-25x20

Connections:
3v3: C102.1, C103.1, C104.1, C105.1, C111.1, C112.1, C202.1, C204.1, C225.1, C226.1, C228.1, C229.1, D201.1, IC102.1, IC102.17, IC104.5, IC105.1, IC202.5, IC206.5, IC207.5, L101.2, P101.1, R108.1, R109.2, TP105.1, Y101.1, Y101.4
5v: C110.1, C215.1, C218.1, IC103.3, IC104.1, IC104.3, IC204.5, R105.1, TP104.1
15v: C211.1, C213.1, IC101.3, IC203.2, R104.1, TP103.1
24v: C106.1, C109.1, C201.1, C203.1, D102.1, D111.1, IC101.1, IC103.1, IC201.3, IC201.5, J102.1, R101.1, R102.1, R201.1, TP101.1
/Flyback/390V: C223.2, C224.2, D205.2, IC205.2, Q202.1, R222.1
/Flyback/400V: C216.2, C219.1, C223.1, C224.1, D203.1, D204.1, IC205.3, IC205.5, R213.1, R218.1, R228.2
/Flyback/HV+: IC205.4, J103.3, R228.1
/GD: IC102.18, IC203.3
/I_IN: IC102.8, IC202.1, IC202.4, TP201.1
/I_OUT: IC102.7, IC206.1, IC206.4, TP205.1
/I_Q: IC102.13, IC204.1, R211.1, R212.1, TP203.1
/LED_FAULT: IC102.27, R106.1
/LED_STAT: IC102.26, R107.1
/SWCLK: IC102.24, P101.4
/SWDIO: IC102.23, P101.2
/UART_RX: IC102.30, IC105.2
/UART_TX: IC102.29, IC105.3, R110.2
/VIN_MON: C101.1, IC102.9, R102.2, R103.1
/VOUT_MON: IC102.6, IC207.1, IC207.4
/V_Q: D201.2, D202.1, IC102.12, IC102.14, R207.2, R208.1
/~RST: IC102.4, P101.10
/~RUN: IC102.25, R109.1, R111.2
GND: C101.2, C102.2, C103.2, C104.2, C105.2, C106.2, C107.2, C108.2, C109.2, C110.2, C111.2, C112.2, C201.2, C202.2, C203.2, C204.2, C205.2, C206.1, C207.1, C208.2, C209.2, C210.2, C211.2, C212.2, C213.2, C215.2, C217.1, C218.2, C221.2, C222.2, C225.2, C226.2, C227.2, C228.2, C229.2, D101.2, D103.1, D104.1, D105.1, D106.1, D107.1, D108.1, D109.2, D110.2, D111.2, D202.2, IC101.2, IC102.16, IC102.31, IC102.32, IC103.2, IC104.2, IC105.4, IC201.2, IC202.2, IC203.4, IC204.2, IC206.2, IC207.2, J101.3, J102.4, J103.1, P101.3, P101.5, P101.9, R103.2, R202.2, R203.2, R205.2, R208.2, R210.2, R217.2, R221.2, R225.2, R226.2, R227.2, T201.6, TP102.1, TP206.1, Y101.2
unnamed: C107.1, C108.1, IC102.5, L101.1
unnamed: C113.1, IC105.8, J104.1
unnamed: C113.2, IC105.5, J104.4
unnamed: C205.1, IC201.1, IC202.3, R202.1
unnamed: C206.2, C207.2, C208.1, C209.1, C210.1, C212.1, C214.1, IC201.4, R201.2, T201.9, T201.10, T201.11, T201.12
unnamed: C214.2, R204.1
unnamed: C216.1, C217.2
unnamed: C219.2, C220.1
unnamed: C220.2, C221.1
unnamed: C222.1, IC207.3, R216.2, R217.1, TP204.1
unnamed: C227.1, IC206.3, Q202.3, R226.1, R227.1
unnamed: D101.1, D102.2, J101.1
unnamed: D103.2, R101.2
unnamed: D104.2, R104.2
unnamed: D105.2, R105.2
unnamed: D106.2, R106.2
unnamed: D107.2, R107.2
unnamed: D108.2, R108.2
unnamed: D109.1, J102.3, R110.1
unnamed: D110.1, J102.2, R111.1
unnamed: D203.2, T201.7
unnamed: D204.2, D205.1
unnamed: IC102.2, Y101.3
unnamed: IC105.6, J104.3
unnamed: IC105.7, J104.2
unnamed: IC203.5, Q201.G, R203.1, TP202.1
unnamed: IC204.3, R209.1
unnamed: IC204.4, R210.1, R211.2, R212.2
unnamed: IC205.1, Q202.2
unnamed: Q201.D, R204.2, R206.1, T201.1, T201.2, T201.3, T201.4, TP207.1
unnamed: Q201.S, R205.1, R209.2
unnamed: R206.2, R207.1
unnamed: R213.2, R214.1
unnamed: R214.2, R215.1
unnamed: R215.2, R216.1
unnamed: R218.2, R219.1
unnamed: R219.2, R220.1
unnamed: R220.2, R221.1
unnamed: R222.2, R223.1
unnamed: R223.2, R224.1
unnamed: R224.2, R225.1

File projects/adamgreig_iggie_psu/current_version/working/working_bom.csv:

"Id";"Designator";"Footprint";"Quantity";"Designation";"Supplier and ref";
1;"C101,C222";"0603";2;"100p";;;
2;"C102,C106,C109,C110,C209,C208";"1210";6;"10µ";;;
3;"C103,C104,C105,C108,C202,C215,C224,C225,C203,C213,C228,C113,C112";"0603";13;"100n";;;
4;"C107,C111,C204,C218,C223,C226,C229";"0603";7;"1µ";;;
5;"C205,C227";"0805";2;"10n";;;
6;"D101";"DO-214AC-SMA";1;"SMAJ58A";;;
7;"D104,D105,D108,D103,D107";"0603-LED";5;"GRN";;;
8;"D109,D110,D111";"0603";3;"ESD_DIODE";;;
9;"D201,D202";"SOD-123";2;"NTS245SFT1G";;;
10;"IC101";"TSR1";1;"TSR 1-24150";;;
11;"IC103";"TSR1";1;"TSR 1-2450";;;
12;"IC104";"SOT-23-5";1;"NCP161";;;
13;"IC202,IC206,IC207";"SOT-23-5";3;"AD8605";;;
14;"J102";"MOLEX-KK-254P-04";1;"CTRL";;;
15;"P101";"FTSH-105-01-L-DV-K";1;"SWD";;;
16;"R101,R103,R104,R109,R206,R207,R217";"0603";7;"10k";;;
17;"R102,R211,R226,R202,R203,R212,R227";"0603";7;"100k";;;
18;"R105,R106,R107,R108,R110,R111,R208,R209,R210";"0603";9;"1k";;;
19;"TP101,TP103,TP104,TP105,TP204,TP205,TP201";"TESTPAD";7;"TESTPAD";;;
20;"X101,X102,X103,X104";"M3_MOUNT";4;"M3 MOUNT";;;
21;"Q202";"SOT-23";1;"PBHV9050T";;;
22;"IC204";"SOT-23-5";1;"AD8065";;;
23;"C201,C211,C210,C212";"1206";4;"1µ";;;
24;"IC201,IC205";"SOT-23-5";2;"INA139";;;
25;"TP206,TP203,TP102,TP202,TP207";"KEYSTONE5016";5;"TESTPAD";;;
26;"J101";"BARRELJACK";1;"PWR_IN";;;
27;"Y101";"XTAL-25x20";1;"25M";;;
28;"J103";"MOLEX-KK-254P-03";1;"HV_OUT";;;
29;"R221,R220,R218,R219";"1206";4;"100k";;;
30;"R222,R224,R225,R215,R214,R223,R216,R213";"1206";8;"499k";;;
31;"C207,C206";"PANASONIC-SMDCAP-G";2;"100µ";;;
32;"C219,C220,C221";"2220";3;"1µ";;;
33;"R228";"1206";1;"500m";;;
34;"D204,D205";"SOT-23";2;"ADR5045";;;
35;"C214";"1206";1;"10n";;;
36;"R204";"1206";1;"4R7";;;
37;"C217,C216";"PANASONIC-SMDCAP-K";2;"68µ";;;
38;"IC203";"SOT-23-5";1;"MCP1416";;;
39;"T201";"GA3459-BL";1;"GA3459-BL";;;
40;"D203";"DPAK_DIODE";1;"STTH512B";;;
41;"R201,R205";"1206";2;"10m";;;
42;"Q201";"D2PAK_GDS";1;"STB45N60DM2AG";;;
43;"X106,X107";"hv";2;"HV SIGN";;;
44;"D102";"DO-214AB-SMC";1;"VSSC520S-M3/9AT";;;
45;"J104";"MOLEX-PICOBLADE-53398-0471";1;"UART";;;
46;"IC105";"SOIC-8";1;"ADuM1201";;;
47;"IC102";"LQFP-32";1;"STM32F334K8T6";;;
48;"D106";"0603-LED";1;"RED";;;
49;"L101";"0603";1;"FB";;;

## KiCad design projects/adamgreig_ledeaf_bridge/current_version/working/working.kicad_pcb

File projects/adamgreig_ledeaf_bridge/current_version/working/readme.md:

# ledeaf
 
## summary 
* id: adamgreig_ledeaf_bridge
* user: adamgreig
* name: ledeaf
* board: bridge
* repo: https://github.com/adamgreig/ledeaf
* src_file_repo_kicad_pcb: bridge/bridge.kicad_pcb
* src_file_repo_kicad_pcb_link: https://github.com/adamgreig/ledeaf/tree/master/bridge/bridge.kicad_pcb
* src_file_repo_kicad_sch: bridge/bridge.kicad_sch
* src_file_repo_kicad_sch_link: https://github.com/adamgreig/ledeaf/tree/master/bridge/bridge.kicad_sch

* src_file_repo_sch: 
* src_file_repo_sch_link: https://github.com/adamgreig/ledeaf/tree/master/
* full details link: https://github.com/oomlout/oomlout_oomp_project_bot_v_2/tree/main/projects/adamgreig_ledeaf_bridge/current_version/working  

## schematic  
  
[schematic (pdf)](working_schematic.pdf) 

## pcb  

[board (pdf)](working.pdf)  

## working_bom
| Id | Designator | Footprint | Quantity | Designation | Supplier and ref |  | None | 
| --- | --- | --- | --- | --- | --- | --- | --- | 
| 1 | J104 | M2_PTH | 1 | DOUT |  |  | [''] | 
| 2 | J103 | M2_PTH | 1 | DIN |  |  | [''] | 
| 3 | J105,J106 | M2_PTH | 2 | 0V |  |  | [''] | 
| 4 | J102,J101 | M2_PTH | 2 | 5V |  |  | [''] | 

## bom_schematic
| Ref | Qnty | Value | Cmp name | Footprint | Description | Vendor | DNP | 
| --- | --- | --- | --- | --- | --- | --- | --- | 
| J101, J102 | 2 | 5V | CONN_01x01 | agg:M2_PTH |  |  |  | 
| J103 | 1 | DIN | CONN_01x01 | agg:M2_PTH |  |  |  | 
| J104 | 1 | DOUT | CONN_01x01 | agg:M2_PTH |  |  |  | 
| J105, J106 | 2 | 0V | CONN_01x01 | agg:M2_PTH |  |  |  |

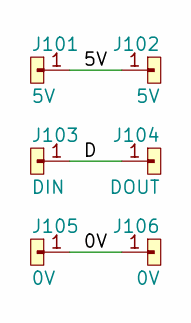
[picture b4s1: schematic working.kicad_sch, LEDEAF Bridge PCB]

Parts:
J101, J102: 5V; M2_PTH
J103: DIN; M2_PTH
J104: DOUT; M2_PTH
J105, J106: 0V; M2_PTH

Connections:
/0V: J105.1, J106.1
/5V: J101.1, J102.1
/D: J103.1, J104.1

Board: 2 copper layers, 6 parts (0 on the bottom side), 3 nets, no tracks yet.

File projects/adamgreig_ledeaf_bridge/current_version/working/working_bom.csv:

"Id";"Designator";"Footprint";"Quantity";"Designation";"Supplier and ref";
1;"J104";"M2_PTH";1;"DOUT";;;
2;"J103";"M2_PTH";1;"DIN";;;
3;"J105,J106";"M2_PTH";2;"0V";;;
4;"J102,J101";"M2_PTH";2;"5V";;;

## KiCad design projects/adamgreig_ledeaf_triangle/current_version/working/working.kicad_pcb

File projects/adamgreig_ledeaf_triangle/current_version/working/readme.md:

# ledeaf
 
## summary 
* id: adamgreig_ledeaf_triangle
* user: adamgreig
* name: ledeaf
* board: triangle
* repo: https://github.com/adamgreig/ledeaf
* src_file_repo_kicad_pcb: triangle/triangle.kicad_pcb
* src_file_repo_kicad_pcb_link: https://github.com/adamgreig/ledeaf/tree/master/triangle/triangle.kicad_pcb
* src_file_repo_kicad_sch: triangle/triangle.kicad_sch
* src_file_repo_kicad_sch_link: https://github.com/adamgreig/ledeaf/tree/master/triangle/triangle.kicad_sch

* src_file_repo_sch: 
* src_file_repo_sch_link: https://github.com/adamgreig/ledeaf/tree/master/
* full details link: https://github.com/oomlout/oomlout_oomp_project_bot_v_2/tree/main/projects/adamgreig_ledeaf_triangle/current_version/working  

## schematic  
  
[schematic (pdf)](working_schematic.pdf) 

## pcb  

[board (pdf)](working.pdf)  

## working_bom
| Id | Designator | Footprint | Quantity | Designation | Supplier and ref |  | None | 
| --- | --- | --- | --- | --- | --- | --- | --- | 
| 1 | X3,X2,X1 | M2.5_HOLE | 3 | TOOLING |  |  | [''] | 
| 2 | C3,C2,C1 | 0402 | 3 | 100n |  |  | [''] | 
| 3 | J2 | M2_PTH | 1 | DIN |  |  | [''] | 
| 4 | J6,J3,J9 | M2_PTH | 3 | 5V |  |  | [''] | 
| 5 | LED1,LED2,LED3 | WS2812B-4020 | 3 | WS2812B-4020 |  |  | [''] | 
| 6 | J1,J7,J4 | M2_PTH | 3 | GND |  |  | [''] | 
| 7 | J5,J8 | M2_PTH | 2 | DOUT |  |  | [''] | 

## bom_schematic
| Ref | Qnty | Value | Cmp name | Footprint | Description | Vendor | DNP | 
| --- | --- | --- | --- | --- | --- | --- | --- | 
| C1, C2, C3 | 3 | 100n | C | agg:0402 |  |  |  | 
| J1, J4, J7 | 3 | GND | CONN_01x01 | agg:M2_PTH |  |  |  | 
| J2 | 1 | DIN | CONN_01x01 | agg:M2_PTH |  |  |  | 
| J3, J6, J9 | 3 | 5V | CONN_01x01 | agg:M2_PTH |  |  |  | 
| J5, J8 | 2 | DOUT | CONN_01x01 | agg:M2_PTH |  |  |  | 
| LED1, LED2, LED3 | 3 | WS2812B-4020 | WS2812B-4020 | agg:WS2812B-4020 | Side-view RGB LED |  |  | 
| X1, X2, X3 | 3 | TOOLING | PART | agg:M2.5_HOLE | Generic placeholder part |  |  |

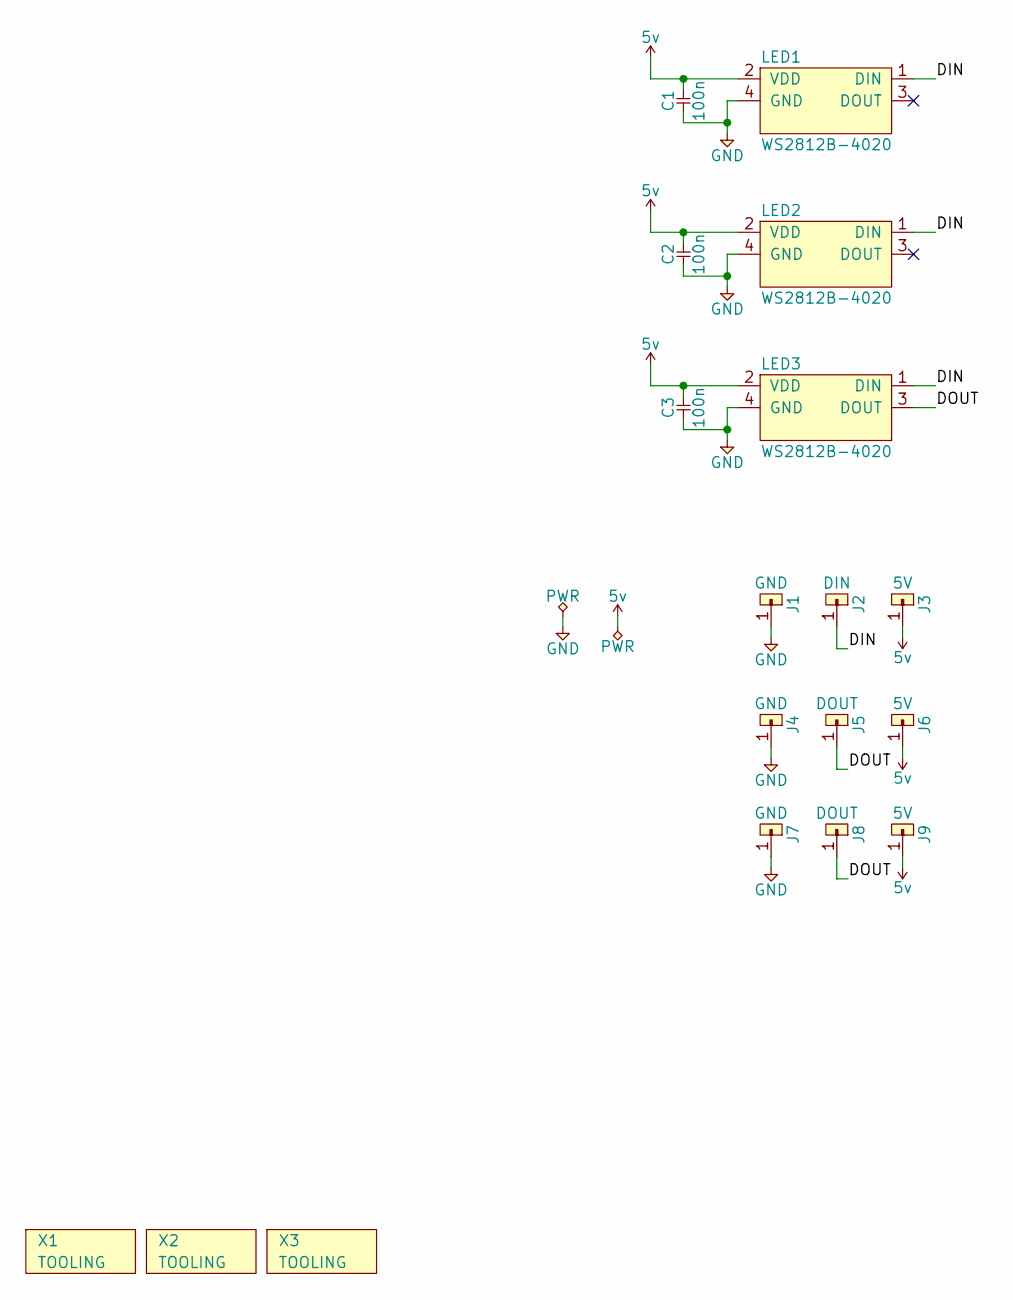
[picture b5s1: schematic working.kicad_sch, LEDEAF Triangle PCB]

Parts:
C1, C2, C3: 100n; 0402; LCSC C1525
J1, J4, J7: GND; M2_PTH
J2: DIN; M2_PTH
J3, J6, J9: 5V; M2_PTH
J5, J8: DOUT; M2_PTH
LED1, LED2, LED3: WS2812B-4020; LCSC C965557
X1, X2, X3: TOOLING; M2.5_HOLE

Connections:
5v: C1.2, C2.2, C3.2, J3.1, J6.1, J9.1, LED1.2 (VDD), LED2.2 (VDD), LED3.2 (VDD)
/DIN: J2.1, LED1.1 (DIN), LED2.1 (DIN), LED3.1 (DIN)
/DOUT: J5.1, J8.1, LED3.3 (DOUT)
GND: C1.1, C2.1, C3.1, J1.1, J4.1, J7.1, LED1.4 (GND), LED2.4 (GND), LED3.4 (GND)
